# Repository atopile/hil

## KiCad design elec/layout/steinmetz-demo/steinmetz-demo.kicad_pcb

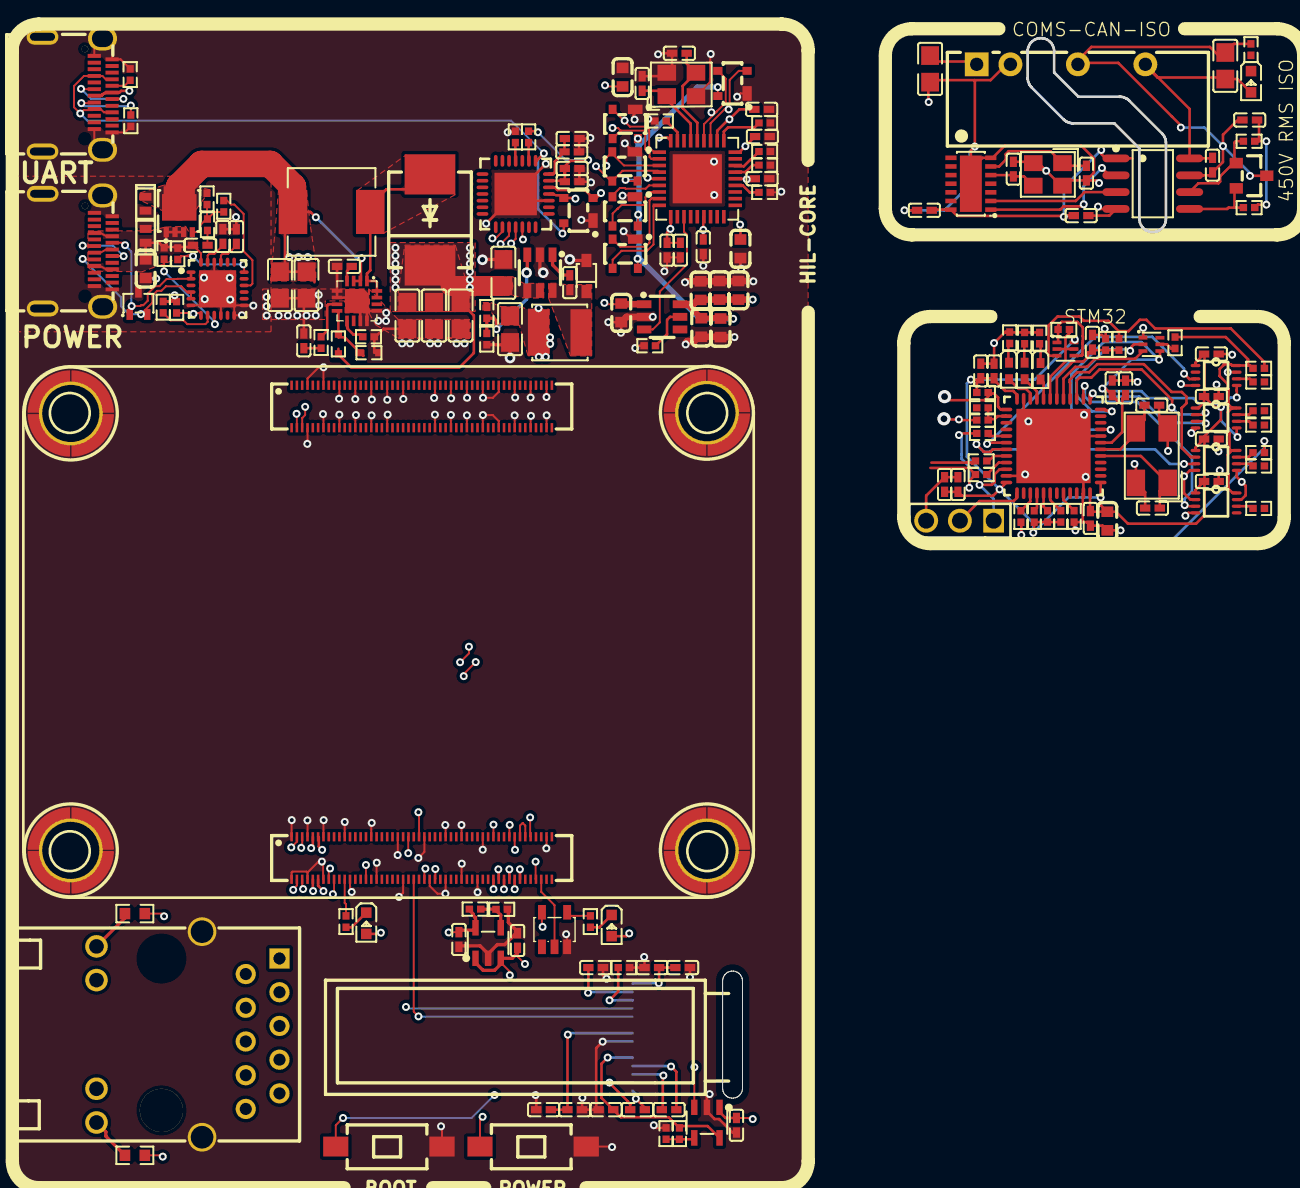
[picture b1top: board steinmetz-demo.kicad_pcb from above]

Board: 2 copper layers, 184 parts (0 on the bottom side), 152 nets.

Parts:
C1: 6.8nF ±10% 50V X7R; C0402-b3ef17
C2, C3, C4, C5, C6, C10, C50: 10µF ±10% 25V X5R; C0805-3b2e55
C7, C18, C41: 4.7µF ±20% 10V X5R; C0402-b3ef17
C8: 470nF ±20% 16V X5R; C0402-b3ef17
C9: 4.7µF ±10% 25V X5R; C0805-3b2e55
C11, C12, C13, C14, C15, C16, C39, C43, C44, C46, C52, C53, C67: 1µF ±10% 25V X5R; C0402-b3ef17
C17, C19, C20, C21, C24, C25, C26, C27, C28, C29, C38, C40, C45, C76: 100nF ±10% 16V X7R; C0402-b3ef17
C22, C23, C32, C33, C34, C35, C36, C37: 10µF ±10% 10V X5R; C0603-bd72f6
C30, C31: 20pF ±5% 50V C0G; C0402-b3ef17
C42: 4.7µF ±10% 35V X5R; C0603-bd72f6
C47, C48: 10pF ±5% 50V C0G; C0402-b3ef17
C49: 2.2µF ±10% 50V X5R; C0805-3b2e55
C51: 4.7nF ±10% 50V X7R; C0402-b3ef17
C62, C63, C64, C65, C68, C69, C70, C71, C72, C73: 100nF ±10% 50V X7R; C0402-b3ef17
C66: 4.7µF ±10% 25V X5R; C0603-bd72f6
C74, C75: 18pF ±5% 50V C0G; C0402-b3ef17
CN1, CN2: CONN-SMD_DF40C-100DS-0.4V-51-ceffa9
D1: SMC_L7.1-W6.2-LS8.1-RD-d9649d
D2: LED0603-RD-YELLOW-5af84a
D3, D14: LED0603-RD-c81ffb
D4, D5, D6, D7, D8, D9: SOT-143_L2.9-W1.3-P1.92-LS2.3-BR-44397f
D10: SOT-323-3_L2.1-W1.3-P1.32-LS2.1-BR-ee9edb
D11, D12: DFN1610-2_L1.6-W1.0-P1.05-RD-57a24e
D13: SOT-23_L2.9-W1.3-P1.90-LS2.4-BR-0c2373
D17, D18, D19: LED0402-R-RD-049f90
H1: HDR-TH_3P-P2.54-V-M-1-04b1f3
L1: IND-SMD_L7.1-W6.6-48b69f
OLED1: OLED-SMD_N087-2832TSWYG02-H14_1-7d3a70
Q1: PDFN3333-8_L3.1-W3.2-P0.65-LS3.4-BL-33e04e
R1, R5, R14, R24, R39, R40, R41, R45, R49, R50, R51, R59, R61: 10kΩ ±1% 62.5mW; R0402-56259e
R2: 180kΩ ±1% 62.5mW; R0402-56259e
R3: 2.49kΩ ±1% 62.5mW; R0402-56259e
R4: 75kΩ ±1% 62.5mW; R0402-56259e
R6: 56kΩ ±1% 62.5mW; R0402-56259e
R7, R8: 2kΩ ±1% 62.5mW; R0402-56259e
R9, R10: 470Ω ±1% 100mW; R0603-ebcab9
R11, R26, R29, R33, R42, R43, R44: 1kΩ ±1% 62.5mW; R0402-56259e
R12: 1.8kΩ ±1% 62.5mW; R0402-56259e
R13: 510kΩ ±1% 62.5mW; R0402-56259e
R15: 25.5kΩ ±1% 62.5mW; R0402-56259e
R16, R17: 5.1kΩ ±1% 62.5mW; R0402-56259e
R18, R19, R21, R22: 33kΩ ±1% 62.5mW; R0402-56259e
R20: 12kΩ ±1% 62.5mW; R0402-56259e
R23: 15kΩ ±1% 62.5mW; R0402-56259e
R25, R27, R28, R60, R62: 4.7kΩ ±1% 62.5mW; R0402-56259e
R30: 100kΩ ±1% 62.5mW; R0402-56259e
R31: 22kΩ ±1% 62.5mW; R0402-56259e
R32, R52, R53, R54, R55, R56, R57, R58, R63: 100Ω ±1% 62.5mW; R0402-56259e
R34, R35: 1MΩ ±1% 62.5mW; R0402-56259e
R46: 1.5kΩ ±1% 62.5mW; R0402-56259e
R47, R48: 22Ω ±1% 62.5mW; R0402-56259e
RJ1: RJ45-TH_HR911130A-5845d4
SW1, SW2: SW-SMD_L6.0-W3.3-LS8.0-cfbaed
U1: VQFN-16_L3.0-W3.0-P0.50-BL-EP1.7-62c35a
U2: SOD-323_L1.8-W1.3-LS2.5-RD
U3: SOT-23-6_L2.9-W1.6-P0.95-LS2.8-BR
U4: 10µH ±20%; IND-SMD_L4.0-W4.0
U5: SOT-23-5_L3.0-W1.7-P0.95-LS2.8-BR-9d80aa
U6, U7, U8, U9: SMD_BD5.6-D4.1-12eb58
U10, U11: SOT-23-5_L3.0-W1.7-P0.95-LS2.8-BL
U12: SQFN-36_L6.0-W6.0-P0.50-BL-EP-5817ac
U13: SOT-23-6_L2.9-W1.6-P0.95-LS2.8-BR-bfc73b
U14: WQFN-28_L5.0-W5.0-P0.50-BL-EP3.2-79d8c5
U15: QFN-24_L4.0-W4.0-P0.50-BL-EP2.8-2a85a7
U16: VDFN-14_L4.5-W3.0-P0.65-BL-EP-99cb5b
U17: CRYSTAL-SMD_4P-L3.2-W2.5-BL-e199c8
U18: PWRM-TH_BXXXXS-2WR3-d8b2fb
U19: SOIC-8_L4.9-W3.9-P1.27-LS6.0-BL-6ccfeb
U24, U25, U26, U27: VSSOP-8_L2.4-W2.1-P0.50-LS3.2-BR-acd3fc
U28: UFQFPN-48_L7.0-W7.0-P0.50-BL-EP5.6-10abf8
U29, U30: SOT-563-6_L1.6-W1.2-P0.5-LS1.6-BL-d9216f
USB1, USB2: USB-C-SMD_TYC-324G-a50b79
X1: CRYSTAL-SMD_4P-L3.2-W2.5-BL-1-d85bc6
X2: OSC-SMD_4P-L5.0-W3.2-BL-ee849f

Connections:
A5: R16.1, USB1.A5
A7: USB2.A7, USB2.B7
B5: R17.1, USB1.B5
B6: USB2.A6, USB2.B6
BOOT0: R45.1, U28.44
C1N: C13.1, OLED1.4
C1P: C13.2, OLED1.3
C2N: C14.1, OLED1.2
C2P: C14.2, OLED1.1
CB: C8.1, U3.1
COMP: R3.1, U1.7
D1: U28.17, U30.3
DIR: U27.5, U28.11
DISCH: R26.2, U15.9
EN_ENh: U12.12, U13.3
FREQ: R4.1, U1.9
G2: U28.12, U30.2
GND: C1.2, C2.2, C3.2, C4.2, C5.2, C6.2, C7.2, C9.2, C10.2, C11.2, C12.2, C15.2, C16.2, C17.2, C18.2, C19.2, C20.2, C21.2, C22.2, C23.2, C24.2, C25.2, C26.2, C27.2, C28.2, C29.2, C30.2, C31.2, C32.2, C33.2, C34.2, C35.2, C36.2, C37.2, C38.2, C39.2, C40.2, C41.2, C42.1, C43.1, C44.1, CN1.1, CN1.4, CN1.7, CN1.11, CN1.16, CN1.21, CN1.26, CN1.30, CN1.33, CN1.37, CN1.49, CN1.65, CN1.68, CN1.71, CN1.74, CN1.79, CN1.84, CN1.89, CN1.94, CN1.97, CN1.100, CN2.4, CN2.7, CN2.10, CN2.13, CN2.16, CN2.19, CN2.22, CN2.28, CN2.31, CN2.34, CN2.37, CN2.40, CN2.43, CN2.46, CN2.49, CN2.52, CN2.55, CN2.58, CN2.61, CN2.64, CN2.67, CN2.70, CN2.73, CN2.82, CN2.85, CN2.88, CN2.91, CN2.94, CN2.97, D4.1, D5.1, D6.1, D7.1, D8.1, D9.1, D10.3, D11.2, D12.2, OLED1.7, R1.2, R4.2, R5.2, R11.2, R13.2, R14.2, R16.2, R17.2, R18.2, R19.2, R20.2, R21.2, R22.2, R23.2, R24.2, RJ1.SHIELD0, RJ1.SHIELD1, SW1.2, SW2.2, U1.5, U1.6, U1.11, U1.12, U1.13, U1.17, U2.2, U3.2, U5.3, U6.1, U6.2, U6.3, U6.4, U7.1, U7.2, U7.3, U7.4, U8.1, U8.2, U8.3, U8.4, U9.1, U9.2, U9.3, U9.4, U10.2, U11.2, U12.37, U13.2, U14.3, U14.29, U15.6, U15.10, U15.12, U15.13, U15.22, U15.25, USB1.1, USB1.2, USB1.3, USB1.4, USB1.A1, USB1.A12, USB1.B1, USB1.B12, USB2.1, USB2.2, USB2.3, USB2.4, USB2.A1, USB2.A12, USB2.B1, USB2.B12, X1.2, X1.4
HS_IND_CFG_SEL1: R21.1, U12.25
ILIM: R23.1, U13.5
IREF: OLED1.12, R13.1
MDI0_: CN1.5, RJ1.P3
MDI0plus: CN1.6, RJ1.P2
MDI2_: CN1.96, RJ1.P6
MDI2plus: CN1.95, RJ1.P5
MDI3plus: CN1.99, RJ1.P8
NRST: C73.1, U28.7
PA8: R46.2, U28.29
PA11: R47.2, U28.32
PA12: R48.2, U28.33
PA13: H1.1, U28.34
PA14: H1.2, U28.37
PB3: R56.1, U28.39
PB4: R39.1, U28.40
PB5: R40.1, U28.41
PB6: R41.1, U28.42
PB12: R49.1, U28.25
POWER_3V3: C12.1, C20.1, C21.1, C22.1, C23.1, C24.1, C25.1, C26.1, C27.1, C28.1, C29.1, OLED1.8, R12.1, U10.5, U12.5, U12.10, U12.15, U12.23, U12.27, U12.29, U12.36
POWER_5V: C10.1, C11.1, C15.1, C32.1, CN1.57, CN1.58, CN1.59, CN1.60, CN1.61, CN1.62, R6.1, U4.2, U10.1, U10.3, U11.1, U11.3, U13.1
POWER_24V: C4.1, C5.1, C6.1, C9.1, D1.1, R2.1, U3.4, U3.5
RBIAS: R20.1, U12.35
RSTh: R25.1, U14.9
S2: R50.2, U29.1, U29.4
SCL_SMBCLK_CFG_SEL0: R18.1, U12.24
SDA_SMBBATA_NON_REM1: R19.1, U12.22
SS: C7.1, U1.4
SUSPENDh: R24.1, U14.11
SUSP_IND_LOCAL_PWR_NON_REM0: R22.1, U12.28
VBUS_EN_SNK: R31.2, U15.16
VBUS_VS_DISCH: R29.2, U15.18
VCCB: R51.1, R63.1, U24.8, U25.8, U26.8, U27.8
VCOMH: C19.1, OLED1.13
Y: R8.2, U5.4
can_transceiver1-CANH: D13.1, R34.1, U19.6
can_transceiver1-CANL: D13.2, R35.2, U19.5
can_transceiver1-rx: U16.2, U19.3
can_transceiver1-tx: U16.1, U19.2
can_transceiver1.regulator.led-cathode: D14.1, R33.1
can_transceiver1.termination-_midpoint: C51.1, R34.2, R35.1
gate: Q1.4, R30.1, R31.1, R32.1
gnd: C50.2, C51.2, C53.2, D13.3, R33.2, U18.4, U19.7
gnd-1: C62.2, C63.2, C64.2, C65.2, C66.2, C67.2, C68.2, C69.2, C70.2, C71.2, C72.2, C73.2, C74.2, C75.2, C76.2, H1.3, R42.2, R43.2, R44.2, R45.2, R59.2, R61.2, U24.2, U24.4, U24.7, U25.4, U26.4, U26.5, U27.2, U27.4, U27.7, U28.8, U28.23, U28.35, U28.47, U28.49, U30.1, X2.2, X2.4
gnd-4: C46.2, C47.2, C48.2, C49.2, C52.2, U16.7, U16.15, U17.2, U17.4, U18.2, U19.4
hil_core-VBUS: D9.4, U14.8, USB1.A4, USB1.A9, USB1.B4, USB1.B9
hil_core-hv: CN1.39, CN1.42, CN1.43, D2.2, D3.2, R9.1, R10.1, U5.5
hil_core-line: CN2.98, D5.3, U12.4
hil_core-line-1: CN1.86, U14.24
hil_core-line-2: D4.3, D9.3, U12.2, U14.4
hil_core-line-3: CN1.77, OLED1.10
hil_core-line-4: CN2.99, D5.2, U12.3
hil_core-line-5: CN1.73, U14.25
hil_core-line-6: CN1.25, U14.23
hil_core-line-7: D8.3, U12.31, USB1.A6, USB1.B6
hil_core-line-8: CN1.75, U14.26
hil_core-line-9: D8.2, U12.30, USB1.A7, USB1.B7
hil_core-line-10: CN1.23, OLED1.11
hil_core-line-11: D4.2, D9.2, U12.1, U14.5
hil_core.boost_24v-FB: R1.1, R2.2, U1.8
hil_core.boost_24v-net: C1.1, R3.2
hil_core.buck_5v-FB: R5.1, R6.2, U3.3
hil_core.buck_5v-cathode: C8.2, U2.1, U3.6, U4.1
hil_core.controller-pins[3]: CN1.2, RJ1.P4
hil_core.controller-pins[5]: CN1.3, RJ1.P7
hil_core.controller-pins[14]: CN1.93, RJ1.12
hil_core.controller-pins[16]: CN1.92, RJ1.13
hil_core.controller-pins[92]: CN1.54, SW1.1
hil_core.controller.cm5-cathode: D2.1, R7.1
hil_core.controller.cm5-cathode-1: D3.1, R8.1
hil_core.controller.cm5-pins[20]: CN1.90, R7.2
hil_core.controller.cm5-pins[89]: CN1.44, CN1.45
hil_core.controller.cm5-pins[94]: CN1.53, U5.2
hil_core.controller.rj45-anode: R9.2, RJ1.11
hil_core.controller.rj45-anode-1: R10.2, RJ1.14
hil_core.ldo_3v3-ADJ_NC: R11.1, R12.2, U10.4
hil_core.oled.regulator_4v-ADJ_NC: R14.1, R15.2, U11.4
hil_core.usb_hub-line: D7.2, U12.8
hil_core.usb_hub-line-1: D6.2, U12.6
hil_core.usb_hub-line-2: D7.3, U12.9
hil_core.usb_hub-line-3: D6.3, U12.7
hil_core.usbpd-VBUS: C42.2, C45.2, D11.1, Q1.1, Q1.2, Q1.3, R26.1, R29.1, U15.24, USB2.A4, USB2.A9, USB2.B4, USB2.B9
hil_core.usbpd-hv: R27.2, R28.2
hil_core.usbpd-line: D10.1, U15.1, U15.2, USB2.A5
hil_core.usbpd-line-1: R27.1, U15.7
hil_core.usbpd-line-2: R28.1, U15.8
hil_core.usbpd-line-3: D10.2, U15.4, U15.5, USB2.B5
hil_core.usbpd.pd_controller-hv: C44.2, U15.23
hil_core.usbpd.pd_controller-hv-1: C43.2, U15.21
hil_core.usbpd.pd_controller-net: C45.1, R32.2
hv: C2.1, C3.1, D12.1, L1.1, Q1.5, Q1.6, Q1.7, Q1.8, Q1.9, R30.2, U1.2, U1.3
hv-1: C62.1, C63.1, C64.1, C65.1, C66.1, C67.1, C68.1, C69.1, C70.1, C71.1, C72.1, R39.2, R40.2, R41.2, R49.2, U24.1, U24.5, U25.1, U25.5, U26.1, U27.1, U28.1, U28.9, U28.24, U28.36, U28.48, U29.6, U30.4
hv-2: C33.1, C34.1, C35.1, C36.1, C37.1, D4.4, D5.4, D6.4, D7.4, D8.4, U13.6
hv-4: C17.1, C18.1, OLED1.14
hv-5: C46.1, C52.1, U16.14, U19.1
hv-6: C16.1, OLED1.5, R15.1, U11.5
hv-8: C40.1, C41.1, R25.2, U14.6
hv-9: C49.1, U18.1
hv-10: C38.1, C39.1, U14.7
hv-12: C50.1, C53.1, D14.2, U18.6, U19.8
jtag_debugger-B1: R52.1, U25.7
jtag_debugger-B1-1: R54.1, U26.7
jtag_debugger-B2: R57.1, U26.6
jtag_debugger-B2-1: R55.1, U27.6
jtag_debugger-B2-2: R53.1, U25.6
jtag_debugger-B2-3: R58.1, U24.6
jtag_debugger-G1: R50.1, U28.19, U29.2, U29.5
jtag_debugger-G1-1: R51.2, U30.5
jtag_debugger-anode: D17.1, U28.20
jtag_debugger-anode-1: D18.1, U28.21
jtag_debugger-anode-2: D19.1, U28.22
jtag_debugger-hv-1: R62.1, R63.2, U29.3
jtag_debugger-line-2: U26.2, U28.16
jtag_debugger-line-3: R59.1, R60.2, U28.26
jtag_debugger-line-4: U26.3, U28.31
jtag_debugger-line-5: R54.2, R56.2
jtag_debugger-line-6: C76.1, R61.1, R62.2, U28.18
jtag_debugger-line-8: U27.3, U28.14
jtag_debugger-line-10: U25.2, U28.15
jtag_debugger-line-11: U24.3, U28.30
jtag_debugger-line-14: R46.1, R48.1
jtag_debugger-line-15: U25.3, U28.13
jtag_debugger.led0-cathode: D17.2, R42.1
jtag_debugger.led1-cathode: D18.2, R43.1
jtag_debugger.led2-cathode: D19.2, R44.1
pins[4]: CN1.98, RJ1.P9
pins[91]: CN1.46, SW2.1
switching_node: D1.2, L1.2, U1.1, U1.15, U1.16
xin: C47.1, U16.6, U17.1
xin-2: C74.1, U28.5, X2.1
xin-3: C30.1, U12.33, X1.1
xout: C75.1, U28.6, X2.3
xout-1: C31.1, U12.32, X1.3
xout-2: C48.1, U16.5, U17.3

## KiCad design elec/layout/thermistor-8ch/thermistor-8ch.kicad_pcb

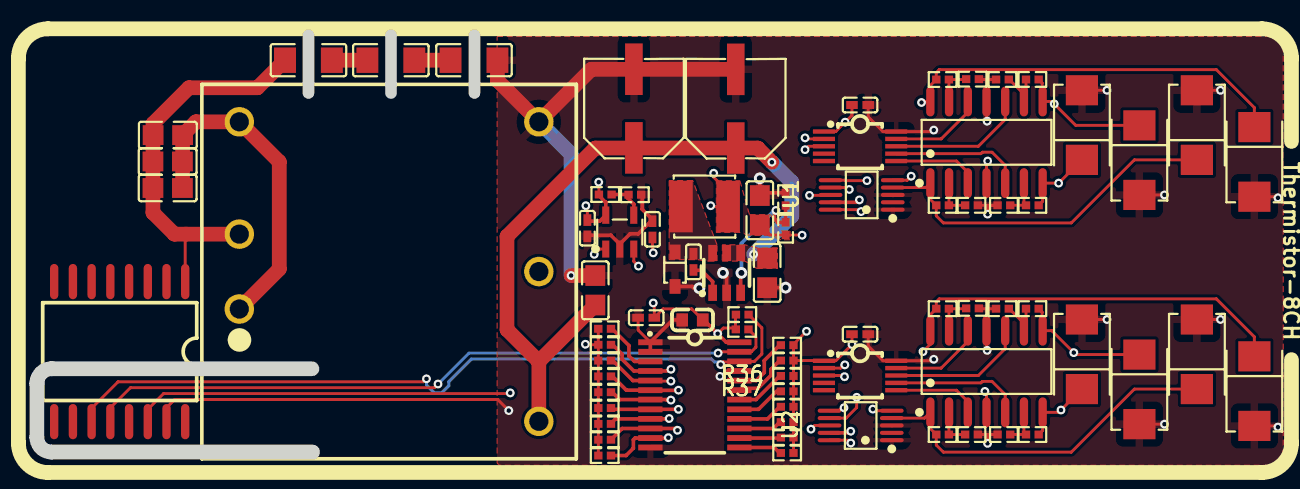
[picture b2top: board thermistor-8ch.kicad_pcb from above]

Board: 4 copper layers, 78 parts (0 on the bottom side), 55 nets.

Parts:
C1: 470nF ±20% 16V X5R; C0402-b3ef17
C2: 4.7µF ±10% 25V X5R; C0805-3b2e55
C3: 10µF ±10% 25V X5R; C0805-3b2e55
C4, C5, C6: 100nF ±10% 16V X7R; C0402-b3ef17
C7: 2.2µF ±10% 25V X5R; C0603-bd72f6
C8, C9: 1µF ±10% 25V X5R; C0402-b3ef17
C10, C11: 10µF ±10% 50V X5R; C0805-3b2e55
C12, C13: 1µF ±10% 50V X7R; C0805-3b2e55
C14, C15: 100µF ±20%; CAP-SMD_BD6.3-L6.6-W6.6-FD-3e301d
C16, C17, C18: 2.2nF ±5% 1kV C0G; C1206-f0a137
D1, D2, D3, D4, D5, D6, D7, D8: SMB_L4.6-W3.6-LS5.3-RD-330cb3
R1: 8.2kΩ ±1% 62.5mW; R0402-56259e
R2: 47kΩ ±1% 62.5mW; R0402-56259e
R3, R4, R5, R6, R7, R8, R9, R10, R11, R12, R13, R14, R15, R16, R17, R18: 100Ω ±1% 62.5mW; R0402-56259e
R19, R20, R21, R22, R23, R24, R25, R26, R27, R28, R29, R30, R31, R32, R33, R34, R35, R36, R37, R38: 10kΩ ±1% 62.5mW; R0402-56259e
R39: 18kΩ ±1% 62.5mW; R0402-56259e
U1, U2: MSOP-10_L3.0-W3.0-P0.50-LS5.0-BL-752175
U3: SOD-323_L1.8-W1.3-LS2.5-RD
U4: SOT-23-6_L2.9-W1.6-P0.95-LS2.8-BR
U5: 10µH ±20%; IND-SMD_L4.0-W4.0
U6, U8: SOIC-14_L8.7-W3.9-P1.27-LS6.0-BL-988152
U7, U9: MSOP-10_L3.0-W3.0-P0.50-LS5.0-TL-ee3c6b
U10: SOIC-16_L10.3-W7.4-P1.27-LS10.3-BL-0756a5
U11: TSSOP-24_L7.8-W4.4-P0.65-LS6.4-BL
U12: SOT-23-5_L3.0-W1.7-P0.95-LS2.8-BL
U13: PWRM-TH_TDPOWER_TDK20-XXSXXWH-ae86e0

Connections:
ADJ_NC: R38.1, R39.2, U12.4
CB: C1.1, U4.1
FB: R1.1, R2.2, U4.3
IN2plus: U6.5, U7.7
IN3plus: U8.10, U9.8
RESET_: R35.1, U11.3
SC4: R27.1, U11.14
SC5: R29.1, U11.16
SC6: R31.1, U11.18
SC7: R33.1, U11.20
SD4: R28.1, U11.13
SD5: R30.1, U11.15
SD6: R32.1, U11.17
SD7: R34.1, U11.19
SW: C1.2, U3.1, U4.6, U5.1
VOUTB: U8.5, U9.7
VOUTC: U6.10, U7.8
dac_1_4-VOUTA: U6.3, U7.6
dac_1_4-VOUTD: U6.12, U7.9
dac_1_4.amplifier-IN1_: R3.1, R4.2, U6.2
dac_1_4.amplifier-IN2_: R5.1, R6.2, U6.6
dac_1_4.amplifier-IN3_: R7.1, R8.2, U6.9
dac_1_4.amplifier-IN4_: R9.1, R10.2, U6.13
dac_5_8-VOUTA: U8.3, U9.6
dac_5_8-VOUTD: U8.12, U9.9
dac_5_8.amplifier-IN1_: R11.1, R12.2, U8.2
dac_5_8.amplifier-IN2_: R13.1, R14.2, U8.6
dac_5_8.amplifier-IN3_: R15.1, R16.2, U8.9
dac_5_8.amplifier-IN4_: R17.1, R18.2, U8.13
gnd: C10.2, C11.2, C12.2, C16.1, U10.1, U13.2
gnd-1: C2.2, C3.2, C4.2, C5.2, C6.2, C7.2, C8.2, C9.2, C13.2, C14.2, C15.2, C18.2, D1.2, D2.2, D3.2, D4.2, D5.2, D6.2, D7.2, D8.2, R1.2, R4.1, R6.1, R8.1, R10.1, R12.1, R14.1, R16.1, R18.1, R38.2, U1.1, U1.3, U2.1, U2.3, U3.2, U4.2, U6.11, U7.10, U8.11, U9.10, U10.15, U11.1, U11.2, U11.12, U11.21, U12.2, U13.4
hv: C2.1, C13.1, C14.1, C15.1, U4.4, U4.5, U13.6
hv-1: C4.1, C5.1, C6.1, C7.1, C9.1, R19.2, R20.2, R21.2, R22.2, R23.2, R24.2, R25.2, R26.2, R27.2, R28.2, R29.2, R30.2, R31.2, R32.2, R33.2, R34.2, R35.2, R36.2, R37.2, R39.1, U7.1, U9.1, U10.14, U11.24, U12.5
hv-3: C3.1, C8.1, R2.1, U1.8, U2.8, U5.2, U6.4, U8.4, U12.1, U12.3
hv-4: C10.1, C11.1, C12.1, U13.1, U13.3
line: R25.1, U1.10, U11.11
line-1: R26.1, U1.9, U11.10
line-2: D8.1, R17.2, U2.7, U8.14
line-3: R36.1, U10.11, U11.22
line-4: D1.1, R3.2, U1.4, U6.1
line-5: R20.1, U7.3, U11.4
line-6: R19.1, U7.2, U11.5
line-7: D7.1, R15.2, U2.6, U8.8
line-8: R22.1, U9.3, U11.6
line-10: D2.1, R5.2, U1.5, U6.7
line-11: R23.1, U2.10, U11.9
line-12: D6.1, R13.2, U2.5, U8.7
line-13: D3.1, R7.2, U1.6, U6.8
line-14: R37.1, U10.12, U11.23
line-15: R24.1, U2.9, U11.8
line-16: D5.1, R11.2, U2.4, U8.1
line-17: R21.1, U9.2, U11.7
line-19: D4.1, R9.2, U1.7, U6.14
regulator_24v_isolated-net: C17.2, C18.1
regulator_24v_isolated-net-1: C16.2, C17.1

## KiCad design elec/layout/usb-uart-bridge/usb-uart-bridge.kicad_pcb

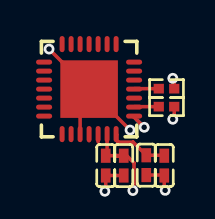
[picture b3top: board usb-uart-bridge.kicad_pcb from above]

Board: 2 copper layers, 7 parts (0 on the bottom side), 5 nets.

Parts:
C1, C3: 100nF ±10% 16V X7R; C0402-b3ef17
C2: 1µF ±10% 25V X5R; C0402-b3ef17
C4: 4.7µF ±20% 10V X5R; C0402-b3ef17
R1: 10kΩ ±1% 62.5mW; R0402-56259e
R2: 4.7kΩ ±1% 62.5mW; R0402-56259e
U1: WQFN-28_L5.0-W5.0-P0.50-BL-EP3.2-79d8c5

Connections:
RSTh: R2.1, U1.9
SUSPENDh: R1.1, U1.11
gnd: C1.2, C2.2, C3.2, C4.2, R1.2, U1.3, U1.29
hv: C3.1, C4.1, R2.2, U1.6
hv-1: C1.1, C2.1, U1.7, U1.8

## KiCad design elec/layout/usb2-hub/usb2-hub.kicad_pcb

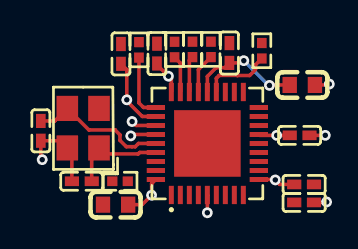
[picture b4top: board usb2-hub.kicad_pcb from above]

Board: 2 copper layers, 18 parts (0 on the bottom side), 10 nets.

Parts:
C1, C2: 20pF ±5% 50V C0G; C0402-b3ef17
C3, C4: 10µF ±20% 6.3V X5R; C0603-bd72f6
C5, C6, C7, C8, C9, C10: 100nF ±10% 16V X7R; C0402-b3ef17
R1, R2, R4, R5: 33kΩ ±1% 62.5mW; R0402-56259e
R3: 12kΩ ±1% 62.5mW; R0402-56259e
R6: 10kΩ ±1% 62.5mW; R0402-56259e
U1: SQFN-36_L6.0-W6.0-P0.50-BL-EP-5817ac
X1: CRYSTAL-SMD_4P-L3.2-W2.5-BL-1-d85bc6

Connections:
HS_IND_CFG_SEL1: R4.1, U1.25
RBIAS: R3.1, U1.35
RESET_N: R6.1, U1.26
SCL_SMBCLK_CFG_SEL0: R1.1, U1.24
SDA_SMBBATA_NON_REM1: R2.1, U1.22
SUSP_IND_LOCAL_PWR_NON_REM0: R5.1, U1.28
gnd: C1.2, C2.2, C3.2, C4.2, C5.2, C6.2, C7.2, C8.2, C9.2, C10.2, R1.2, R2.2, R3.2, R4.2, R5.2, U1.37, X1.2, X1.4
hv: C3.1, C4.1, C5.1, C6.1, C7.1, C8.1, C9.1, C10.1, R6.2, U1.5, U1.10, U1.15, U1.23, U1.27, U1.29, U1.36
xin: C1.1, U1.33, X1.1
xout: C2.1, U1.32, X1.3

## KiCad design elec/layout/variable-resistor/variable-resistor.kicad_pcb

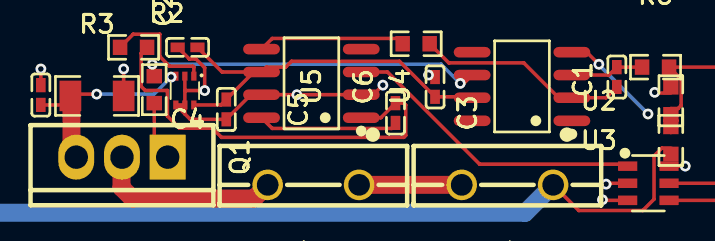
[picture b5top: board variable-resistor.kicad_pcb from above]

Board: 2 copper layers, 20 parts (0 on the bottom side), 16 nets.

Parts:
C1, C2, C3, C4, C5, C6: 1pF 50V C0G; C0402-b3ef17
Q1: TO-220-3_L10.0-W4.5-P2.54-T-277d92
R1, R2, R5, R6: 100Ω ±1% 100mW; R0603-ebcab9
R3: 100mΩ ±1% 250mW; R1206-bdb864
R4, R7: TO-220-2_L10.4-W3.2-P5.08-L-bf0258
U1: SOT-23-6_L2.9-W1.6-P0.95-LS2.8-BL
U2: 1kΩ ±1% 100mW; R0603-ebcab9
U3: 10kΩ ±1% 100mW; R0603-ebcab9
U4: BW CMRR Ib Vos GBW Iout SR; SOIC-8_L4.9-W3.9-P1.27-LS6.0-BL-6ccfeb
U5: SOIC-8_L4.9-W3.9-P1.27-LS6.0-BL-6ccfeb
U6: SOT-563_L1.6-W1.2-P0.50-LS1.6-TL

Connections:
Gain: U1.1, U5.3
VOUT: R5.1, U5.5
_In: C3.2, U5.8
base: Q1.1, R1.1
collector: Q1.2, R7.2
emitter: C2.2, Q1.3, R3.1, U6.3
gnd: C2.1, C4.2, C5.2, C6.2, R3.2, U1.2, U1.6, U2.2, U4.4, U5.2, U5.7, U6.2, U6.4, U6.5
hv-1: R4.1, U3.1
inverting_input: C1.1, R5.2, U4.2
line: R2.1, U6.1
line-3: R6.2, U2.1, U3.2
net: R4.2, R7.1
non_inverting_input: C1.2, R6.1, U4.3
output: R1.2, U4.6
plusIn: C3.1, R2.2, U5.1
plusVS: C4.1, C5.1, C6.1, U4.7, U5.6, U6.6

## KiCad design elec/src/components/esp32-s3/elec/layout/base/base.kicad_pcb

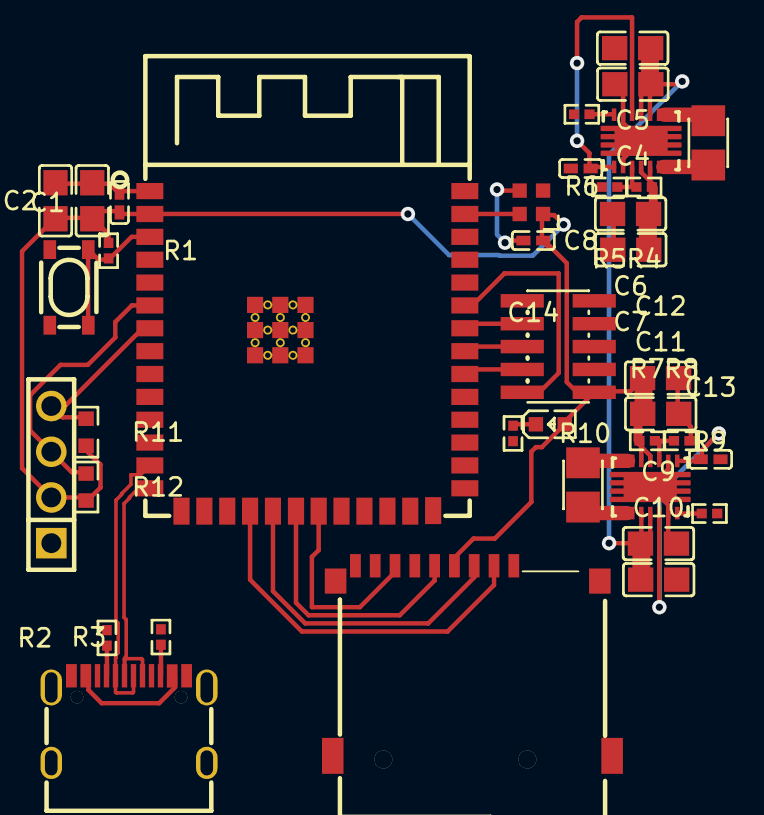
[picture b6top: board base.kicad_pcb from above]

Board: 2 copper layers, 38 parts (0 on the bottom side), 32 nets.

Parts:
C1, C8, C13, C14: 100nF ±10% 16V X7R; C0402-b3ef17
C2, C3, C4, C5, C6, C7, C9, C10, C11, C12: 10µF ±10% 25V X5R; C0805-3b2e55
L1, L2: IND-SMD_L2.5-W2.0_WPN252012H
LED1: LED0603-RD
R1: 10kΩ ±1% 62.5mW; R0402-56259e
R2, R3: 4.7kΩ ±1% 62.5mW; R0402-56259e
R4, R5, R7, R8, R10: 1kΩ ±1% 62.5mW; R0402-56259e
R6, R9: 1MΩ ±1% 62.5mW; R0402-56259e
R11, R12: 2.7kΩ ±1% 100mW; R0603-ebcab9
U1: WIRELM-SMD_ESP32-S3-WROOM-1
U2: KEY-SMD_4P-L4.2-W3.2-P2.20-LS4.6
U3: HDR-SMD_10P-P1.27-V-M-R2-C5-LS5.3
U4: USB-C-SMD_KH-TYPE-C-16P
U5, U6: VSON-14_L4.0-W3.0-P0.50-BL-EP_TI_DSJ
U7: TF-SMD_TF-01A
U8: LED-SMD_4P-L2.0-W2.0-BR
U9: HDR-TH_4P-P2.54-V-F

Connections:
B5: R3.1, U4.B5
CC1: R2.1, U4.A5
EN: C8.1, U5.1, U5.12
L1: L2.1, U6.8, U6.9
L1-1: L1.1, U5.8, U5.9
L2: L1.2, U5.6, U5.7
L2-1: L2.2, U6.6, U6.7
VBUS: U4.A4, U4.A9, U4.B4, U4.B9
VINA: C13.1, U6.1, U6.12
_3v3_reg-PG: R9.1, U6.14
_3v3_reg-out: R7.2, R8.1, U6.3
_5v_reg-PG: R6.1, U5.14
_5v_reg-out: R4.2, R5.1, U5.3
cathode: LED1.1, R10.1
cs: U1.18, U7.2
gnd: C1.2, C2.2, C3.2, C4.2, C5.2, C6.2, C7.2, C8.2, C9.2, C10.2, C11.2, C12.2, C13.2, C14.2, R2.2, R3.2, R5.2, R6.2, R8.2, R9.2, R10.2, U1.1, U1.40, U1.41, U2.3, U2.4, U3.3, U3.5, U3.9, U4.1, U4.2, U4.3, U4.4, U4.A1, U4.A12, U4.B1, U4.B12, U5.2, U5.13, U5.15, U6.2, U6.13, U6.15, U7.6, U7.10, U7.11, U7.12, U7.13, U8.3, U9.1
hv: C1.1, C2.1, C3.1, C11.1, C12.1, C14.1, LED1.2, R1.1, R7.1, R11.2, R12.2, U1.2, U3.1, U6.4, U6.5, U7.4, U8.1, U9.2
hv-1: C4.1, C5.1, C9.1, C10.1, U5.10, U5.11, U6.10, U6.11
hv-2: C6.1, C7.1, R4.1, U5.4, U5.5
in: R1.2, U1.3, U2.1, U2.2
io: U1.39, U8.4
line: R11.1, U1.7, U9.4
line-1: R12.1, U1.6, U9.3
miso: U1.21, U7.7
mosi: U1.19, U7.3
sck: U1.20, U7.5
tck: U1.32, U3.4
tdi: U1.34, U3.8
tdo: U1.33, U3.6
tms: U1.35, U3.2
usb+: U1.14, U4.A6, U4.B6
usb-: U1.13, U4.A7, U4.B7

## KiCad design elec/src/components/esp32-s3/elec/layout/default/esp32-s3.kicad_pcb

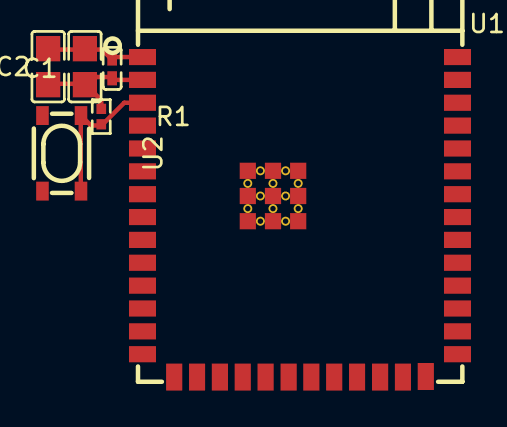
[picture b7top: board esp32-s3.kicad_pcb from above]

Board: 2 copper layers, 6 parts (0 on the bottom side), 3 nets.

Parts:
C1: 100nF ±10% 16V X7R; C0402-b3ef17
C2, C3: 10µF ±10% 25V X5R; C0805-3b2e55
R1: 10kΩ ±1% 62.5mW; R0402-56259e
U1: WIRELM-SMD_ESP32-S3-WROOM-1
U2: KEY-SMD_4P-L4.2-W3.2-P2.20-LS4.6

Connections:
gnd: C1.2, C2.2, C3.2, U1.1, U1.40, U1.41, U2.3, U2.4
hv: C1.1, C2.1, C3.1, R1.1, U1.2
in: R1.2, U1.3, U2.1, U2.2
